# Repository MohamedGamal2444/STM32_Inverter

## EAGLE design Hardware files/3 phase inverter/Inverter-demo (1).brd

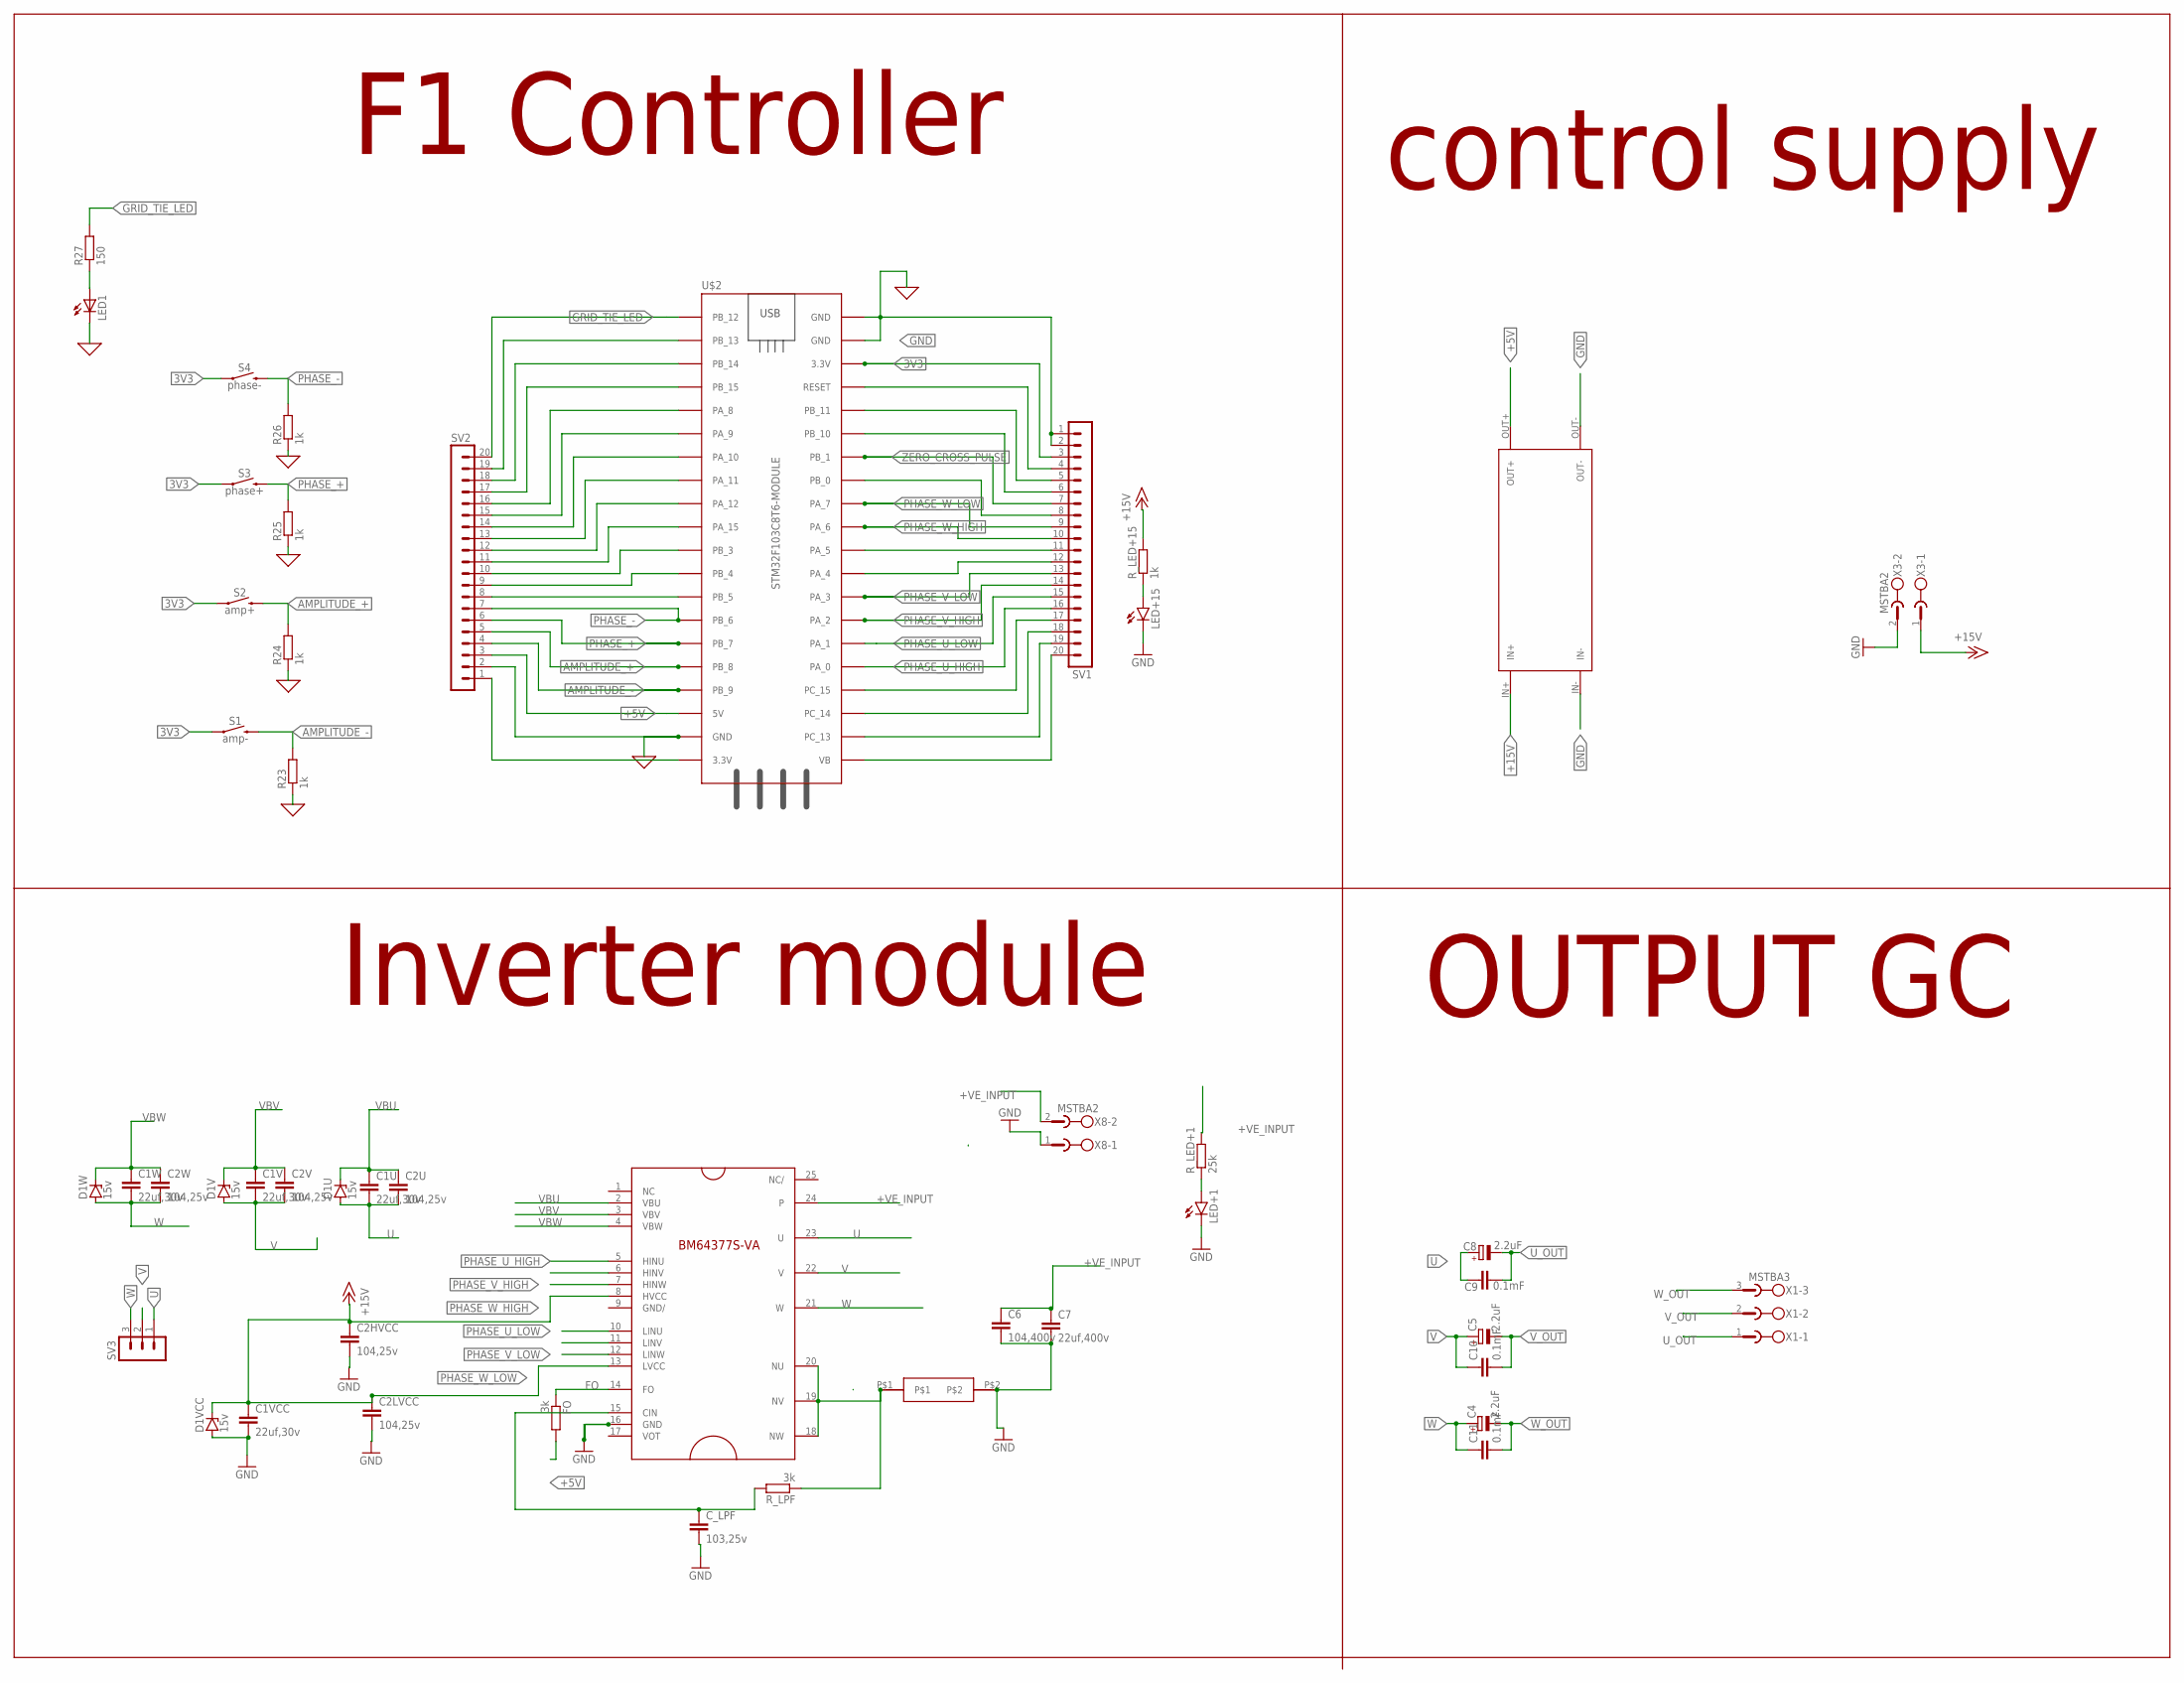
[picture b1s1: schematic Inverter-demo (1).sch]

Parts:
C1U, C1V, C1VCC, C1W: 22uf,30v; C050-025X075
C2HVCC, C2LVCC, C2U, C2V, C2W: 104,25v; C050-025X075
C4, C5, C8: 2.2uF; E3,5-8
C6: 104,400v; C050-025X075
C7: 22uf,400v; C050-025X075
C9, C10, C11: 0.1mF; C5B5
C_LPF: 103,25v; C050-025X075
D1U, D1V, D1VCC, D1W: 15v; DO34Z7
FO: 3k; 0207/10
LED1: LED3MM
LED+1, LED+15: LED5MM
R23, R24, R25, R26: 1k; 0207/10
R27: 150; 0207/10
R_LED+1: 25k; 0207/10
R_LED+15: 1k; 0207/10
R_LPF: 3k; 0207/10
S1: amp-; TACTILE_SWITCH_PTH_6.0MM
S2: amp+; TACTILE_SWITCH_PTH_6.0MM
S3: phase+; TACTILE_SWITCH_PTH_6.0MM
S4: phase-; TACTILE_SWITCH_PTH_6.0MM
SV1, SV2: MA20-1
SV3: MA03-1
U$1: BM64377S-VATHROUGH_HOLE; IPM-BM64377S-VA
U$2: STM32F103C8T6-MODULE
U$3: SMALLSHUNT
U$4: XL4015_DC-DC_CONVERTER
X1: MSTBA3
X3, X8: MSTBA2

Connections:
3V3: S1.1, S2.1, S3.1, S4.1, SV1.3, U$2.3.3V_2 (3.3V)
+5V: FO.2, SV2.3, U$2.5V, U$4.OUT+
+15V: C1VCC.1, C2HVCC.1, C2LVCC.1, D1VCC.C, R_LED+15.2, U$1.8 (HVCC), U$1.13 (LVCC), U$4.IN+, X3.1
+VE_INPUT: C6.1, C7.1, R_LED+1.2, U$1.24, X8.2
AMPLITUDE_+: R24.2, S2.3 (2), SV2.5, U$2.PB_8
AMPLITUDE_-: R23.2, S1.3 (2), SV2.4, U$2.PB_9
FO: FO.1, U$1.14 (FO)
GND: C1VCC.2, C2HVCC.2, C2LVCC.2, C6.2, C7.2, C_LPF.2, D1VCC.A, LED1.K (C), LED+1.K (C), LED+15.K (C), R23.1, R24.1, R25.1, R26.1, SV1.1, SV1.2, SV2.2, U$1.16 (GND), U$2.GND_1 (GND), U$2.GND_2 (GND), U$2.GND_3 (GND), U$3.P$2, U$4.IN-, U$4.OUT-, X3.2, X8.1
GRID_TIE_LED: R27.2, SV2.20, U$2.PB_12
unnamed: LED+1.A, R_LED+1.1
unnamed: C_LPF.1, R_LPF.2, U$1.15 (CIN)
unnamed: R_LPF.1, U$1.18 (NW), U$1.19 (NV), U$1.20 (NU), U$3.P$1
unnamed: SV2.19, U$2.PB_13
unnamed: SV2.18, U$2.PB_14
unnamed: SV2.17, U$2.PB_15
unnamed: SV2.16, U$2.PA_8
unnamed: SV2.15, U$2.PA_9
unnamed: SV2.14, U$2.PA_10
unnamed: SV2.13, U$2.PA_11
unnamed: SV2.12, U$2.PA_12
unnamed: SV2.11, U$2.PA_15
unnamed: SV2.10, U$2.PB_3
unnamed: SV2.9, U$2.PB_4
unnamed: LED1.A, R27.1
unnamed: SV2.8, U$2.PB_5
unnamed: LED+15.A, R_LED+15.1
unnamed: SV2.1, U$2.3.3V_1 (3.3V)
unnamed: SV1.20, U$2.VB
unnamed: SV1.19, U$2.PC_13
unnamed: SV1.18, U$2.PC_14
unnamed: SV1.17, U$2.PC_15
unnamed: SV1.12, U$2.PA_4
unnamed: SV1.11, U$2.PA_5
unnamed: SV1.8, U$2.PB_0
unnamed: SV1.6, U$2.PB_10
unnamed: SV1.5, U$2.PB_11
unnamed: SV1.4, U$2.RESET
PHASE_+: R25.2, S3.3 (2), SV2.6, U$2.PB_7
PHASE_-: R26.2, S4.3 (2), SV2.7, U$2.PB_6
PHASE_U_HIGH: SV1.16, U$1.5 (HINU), U$2.PA_0
PHASE_U_LOW: SV1.15, U$1.10 (LINU), U$2.PA_1
PHASE_V_HIGH: SV1.14, U$1.6 (HINV), U$2.PA_2
PHASE_V_LOW: SV1.13, U$1.11 (LINV), U$2.PA_3
PHASE_W_HIGH: SV1.10, U$1.7 (HINW), U$2.PA_6
PHASE_W_LOW: SV1.9, U$1.12 (LINW), U$2.PA_7
U: C1U.2, C2U.2, C8.+, C9.1, D1U.A, SV3.1, U$1.23 (U)
U_OUT: C8.-, C9.2, X1.1
V: C1V.2, C2V.2, C5.+, C10.1, D1V.A, SV3.2, U$1.22 (V)
VBU: C1U.1, C2U.1, D1U.C, U$1.2 (VBU)
VBV: C1V.1, C2V.1, D1V.C, U$1.3 (VBV)
VBW: C1W.1, C2W.1, D1W.C, U$1.4 (VBW)
V_OUT: C5.-, C10.2, X1.2
W: C1W.2, C2W.2, C4.+, C11.1, D1W.A, SV3.3, U$1.21 (W)
W_OUT: C4.-, C11.2, X1.3
ZERO_CROSS_PULSE: SV1.7, U$2.PB_1

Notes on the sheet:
F1 Controller
control supply
OUTPUT GC
Inverter module

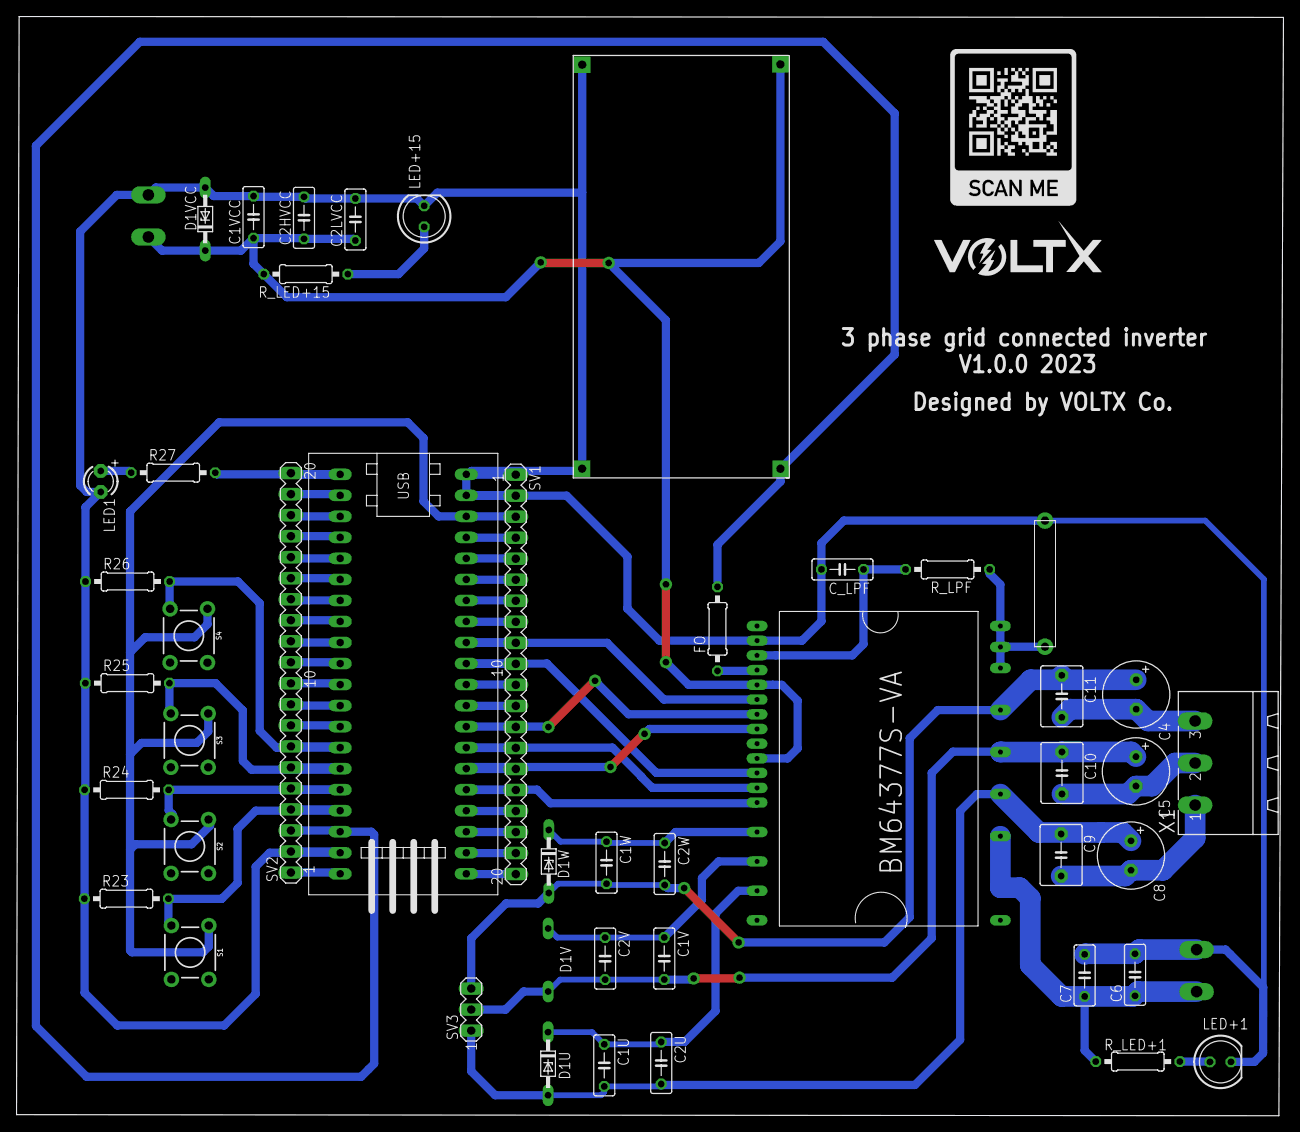
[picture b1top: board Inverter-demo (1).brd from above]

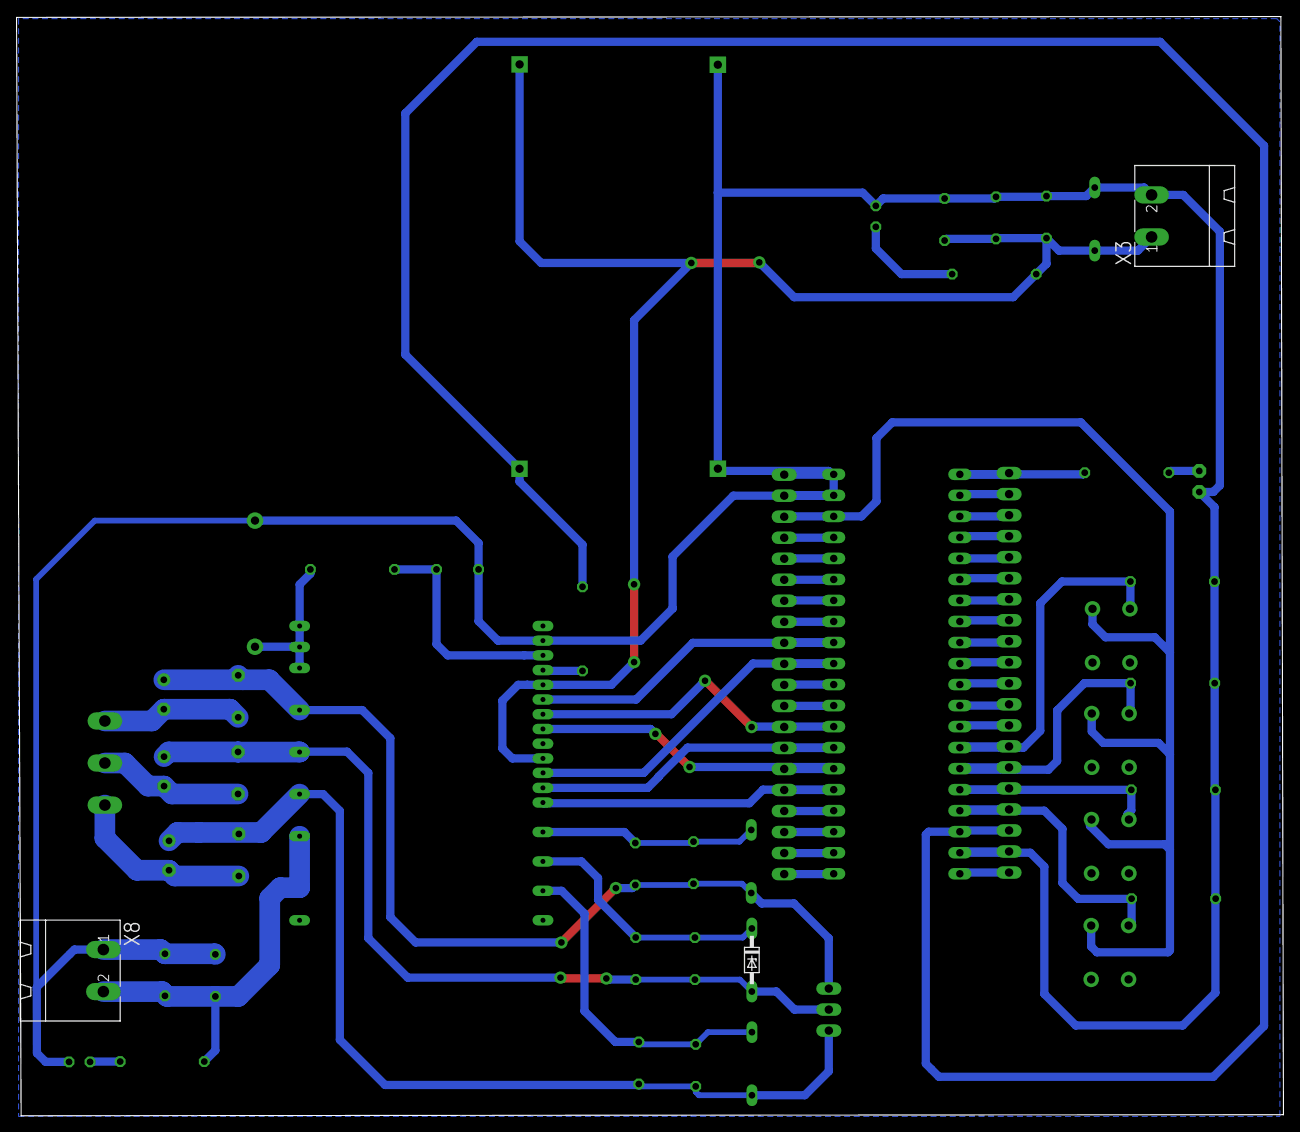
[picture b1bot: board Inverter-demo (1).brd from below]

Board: 2 copper layers, 153.1 x 132.8 mm, 50 parts (3 on the bottom side), 55 nets.

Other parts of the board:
U$8: VOLTX_LOGO_0.8
U$9: SCAN2

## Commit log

2023-06-10 file updates and board update to work with the module BM64377s
    file updates and board update to work with the module BM64377s

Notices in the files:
parts and their libraries:
SparkFun-Switches: Licensing: Creative Commons ShareAlike 4.0 International - https://creativecommons.org/licenses/by-sa/4.0
